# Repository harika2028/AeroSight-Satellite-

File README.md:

🛰️ AeroSight

Satellite Weather Detection & Orbital Object Tracking

<p align="center">
  <b>A Software-Only 3U CubeSat Digital Twin</b><br/>
  Exploring AI, satellite electronics, orbital simulation, and digital design with open-source tools.
</p>---

🌍 Project Overview

AeroSight is a software-only digital twin of a 3U CubeSat (10 × 10 × 30 cm) designed to demonstrate how satellite subsystems can work together in a simulated environment.

It combines AI-based image analysis, orbital mechanics, satellite structure modeling, PCB design, antenna analysis, and Verilog-based digital logic. The system includes a Python processing pipeline, SQLite database, interactive dashboard, and 3D satellite visualization.

«💡 Mission: Explore the design and integration of a satellite system using a laptop and free, open-source engineering tools.»

🪐 Project Gallery

Add your actual project screenshots to the "assets/" folder and update these paths.

🛰️ Satellite Model| 🌎 Orbital Simulation
"3D Satellite" (assets/satellite-model.png)| "Orbit Map" (assets/orbit-map.png)
3U CubeSat structure| Simulated ground track

🤖 AI Detection| 📊 Dashboard
"AI Detection" (assets/object-detection.png)| "Dashboard" (assets/dashboard.png)
Object detection results| Analysis and orbital data

🔌 Power PCB| 💻 Digital Chip
"PCB Design" (assets/power-pcb.png)| "Verilog Waveform" (assets/beacon-waveform.png)
KiCad power board| Beacon timer simulation

✨ Key Features

- 🌦️ Weather Classification — Estimates weather conditions using image color-based rules.
- 🎯 Object Detection — Uses pretrained YOLOv8n to identify objects in images.
- 🗃️ Data Management — Records analysis results in SQLite.
- 📈 Interactive Dashboard — Displays metrics, charts, annotated images, and orbital tracks.
- 🌎 Orbit Simulation — Models a 500 km sun-synchronous orbit.
- 🧩 Satellite CAD Model — Designs the 3U satellite structure in FreeCAD.
- 🔋 Power Electronics — Designs and verifies a solar-input battery charging and regulation circuit.
- 📡 Antenna Analysis — Calculates the theoretical radiation pattern of a 437 MHz UHF dipole.
- ⚙️ Digital Logic — Implements and simulates a beacon timer using Verilog.
- 🎨 3D Visualization — Renders the satellite above Earth using Blender and Three.js.

🏗️ System Architecture

                   🛰️ AEROSIGHT
                        |
       +----------------+----------------+
       |                |                |
   🤖 AI Payload    🌎 Orbit Model   🔧 Satellite Design
       |                |                |
   Image Analysis    Ground Track     CAD / PCB / Antenna
       |                |                |
       +----------------+----------------+
                        |
                🐍 Python Processing
                        |
                  🗃️ SQLite Database
                        |
                 📊 Streamlit Dashboard
                        |
                 🎨 3D Visualization

🛠️ Technology Stack

<p>

</p>Subsystem| Technologies
AI and image processing| Python, OpenCV, YOLOv8, PyTorch
Data and dashboard| SQLite, Pandas, Streamlit
Orbital simulation| Python, NumPy, Matplotlib
Satellite structure| FreeCAD
Power electronics| KiCad
Digital chip| Verilog, Icarus Verilog, Verilator, GTKWave, Yosys
Visualization| Blender, Three.js

🔄 How It Works

1. 📷 Input images are placed in the photos directory.
2. 🤖 The software estimates weather conditions and detects recognizable objects.
3. 🗃️ Results are stored in SQLite, and annotated images are saved.
4. 🌎 An orbital simulation generates satellite latitude and longitude coordinates.
5. 📊 The dashboard presents analysis results and the simulated ground track.
6. 🔧 Separate engineering modules model the satellite structure, PCB, antenna, and beacon timer.
7. 🎨 Blender and Three.js bring the virtual satellite and Earth into a visual overview.

📊 Simulation Results

Parameter| Result
Satellite size| 10 × 10 × 30 cm
Orbital altitude| 500 km
Orbital inclination| 97.4°
Orbital period| Approximately 94.6 minutes
Antenna frequency| 437 MHz
Beacon timer| Pulse every 8 clock cycles in simulation
Logic synthesis| 94 cells reported by Yosys
PCB verification| 0 DRC errors, 0 warnings, 0 unconnected items

Three test photographs were processed. Object detections were recorded for two images, while weather labels were generated for all three. These are initial simulation results, not evidence of flight performance.

📁 Repository Structure

AeroSight/
├── assets/                 # Project screenshots and images
├── photos/                 # Input photographs
├── outputs/                # Annotated images
├── chip/
│   ├── beacon.v            # Verilog timer
│   └── tb.v                # Testbench
├── detect.py               # Image processing pipeline
├── dashboard.py            # Streamlit dashboard
├── orbit.py                # Orbital simulation
├── antenna.py              # Antenna analysis
├── freecad_body.py         # Satellite CAD model
├── requirements.txt        # Python dependencies
└── README.md

Adjust the structure to match the files actually present in your repository.

🚀 Getting Started

Prerequisites

- Windows 11 and Python 3.12
- Visual Studio Code
- Python libraries: OpenCV, Ultralytics, PyTorch, NumPy, Pandas, Streamlit, and Matplotlib
- FreeCAD, KiCad, and Blender for the engineering models
- WSL2 Ubuntu and digital design tools for the Verilog workflow

Installation

git clone YOUR_REPOSITORY_URL
cd AeroSight

python -m venv venv

Activate the environment on Windows:

.\venv\Scripts\Activate.ps1

Install the Python dependencies:

pip install opencv-python ultralytics pandas streamlit matplotlib numpy
pip install torch torchvision --index-url https://download.pytorch.org/whl/cpu

Run the image-processing pipeline

python detect.py

Launch the dashboard

streamlit run dashboard.py

Generate the orbit data

python orbit.py

Generate the antenna pattern

python antenna.py

The commands assume the files and module names match your local implementation. Add any missing setup steps needed by your actual repository.

⚠️ Limitations

- The satellite is a software-only digital twin.
- Weather classification uses color-based rules rather than a trained weather model.
- The orbit is idealized and does not include all real-world orbital perturbations.
- Antenna results are theoretical.
- The beacon chip has been simulated and synthesized but has not been fabricated or physically laid out.

🔮 Future Enhancements

- 🌦️ Train a weather classifier on real satellite imagery.
- 🛰️ Integrate real TLE-based orbit tracking.
- 🎯 Track objects across successive images.
- ⚙️ Explore RTL-to-GDSII implementation using OpenLane.
- 📡 Perform full-wave antenna simulation using openEMS.
- 🧠 Explore RISC-V-based onboard processing.
- 🌐 Add a ground-station communication workflow.

👩‍💻 Author

Niharika Yarasu
Electronics and Communication Engineering Graduate

- 💻 "GitHub" (https://github.com/harika2028)
- 🌐 "Portfolio" (https://harika2028.github.io/niha-portfolio/)
- 🔗 "LinkedIn" (https://www.linkedin.com/in/yarasu-neharika/)

🙏 Acknowledgements

Thanks to the developers and communities behind Python, OpenCV, PyTorch, Ultralytics, Streamlit, SQLite, FreeCAD, KiCad, Icarus Verilog, Verilator, GTKWave, Yosys, Blender, and Three.js.

---

<p align="center">
  <b>🛰️ AeroSight — Learned it. Built it. Did it.</b><br/>
  <i>Dreams don’t need a lab to start.</i>
</p># AeroSight-Satellite-
Developed AeroSight, a software-only 3U CubeSat digital twin integrating AI-based weather classification, YOLOv8 object detection, orbital simulation, satellite structure modeling, PCB design, and Verilog-based digital chip simulation, with an interactive dashboard and 3D visualization using open-source tools.

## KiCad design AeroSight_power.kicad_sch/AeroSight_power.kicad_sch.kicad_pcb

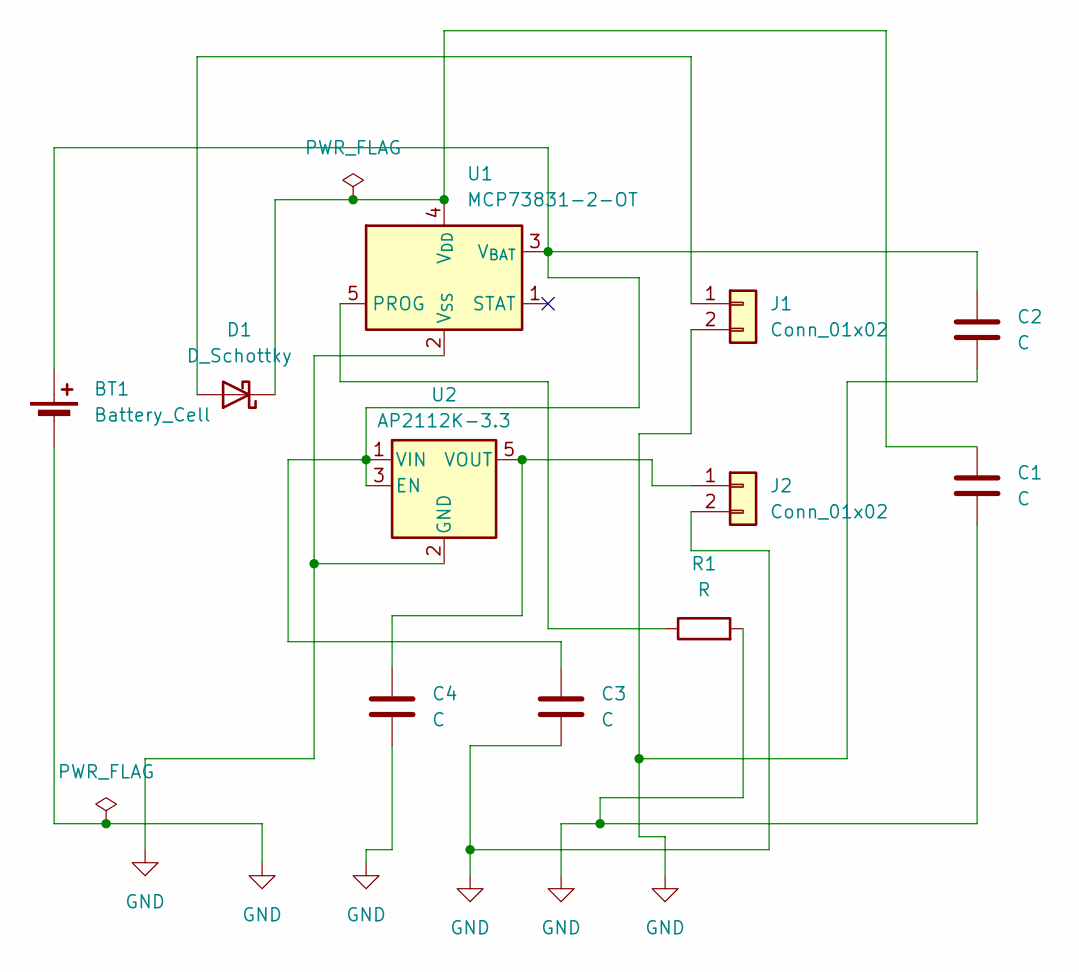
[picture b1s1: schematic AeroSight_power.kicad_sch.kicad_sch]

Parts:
BT1: Battery_Cell; PinHeader_1x02_P2.54mm_Vertical
C1, C2, C3, C4: C; C_0805_2012Metric
D1: D_Schottky; D_SOD-123
J1, J2: Conn_01x02; PinHeader_1x02_P2.54mm_Vertical
R1: R; R_0805_2012Metric
U1: MCP73831-2-OT; SOT-23-5
U2: AP2112K-3.3; SOT-23-5

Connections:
GND: BT1.2 (-), C1.2, C2.2, C3.2, C4.2, J1.2, J2.2, R1.2, U1.2 (V_{SS}), U2.2 (GND)
unnamed: BT1.1 (+), C2.1, C3.1, U1.3 (V_{BAT}), U2.1 (VIN), U2.3 (EN)
unnamed: D1.2 (A), J1.1
unnamed: C1.1, D1.1 (K), U1.4 (V_{DD})
unnamed: C4.1, J2.1, U2.5 (VOUT)
unnamed: R1.1, U1.5 (PROG)

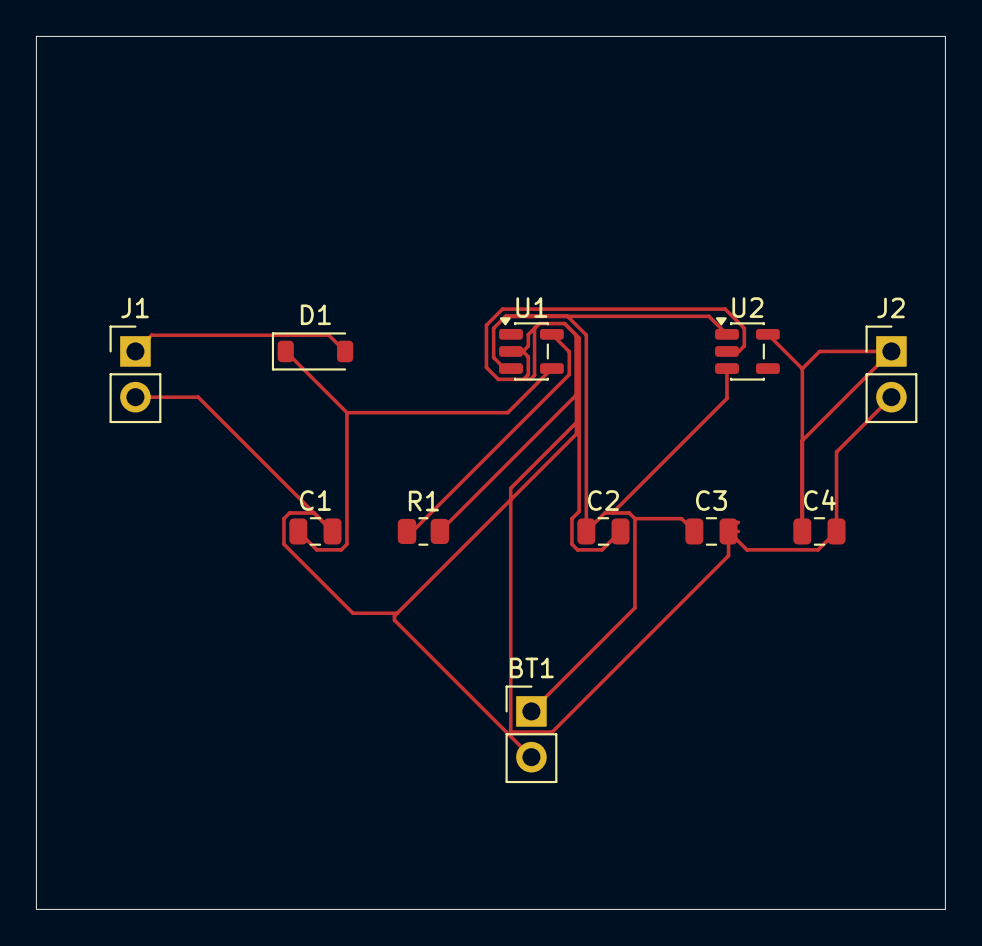
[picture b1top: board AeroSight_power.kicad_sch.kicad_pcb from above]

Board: 2 copper layers, 50.5 x 48.5 mm, 11 parts (0 on the bottom side), 6 nets.
